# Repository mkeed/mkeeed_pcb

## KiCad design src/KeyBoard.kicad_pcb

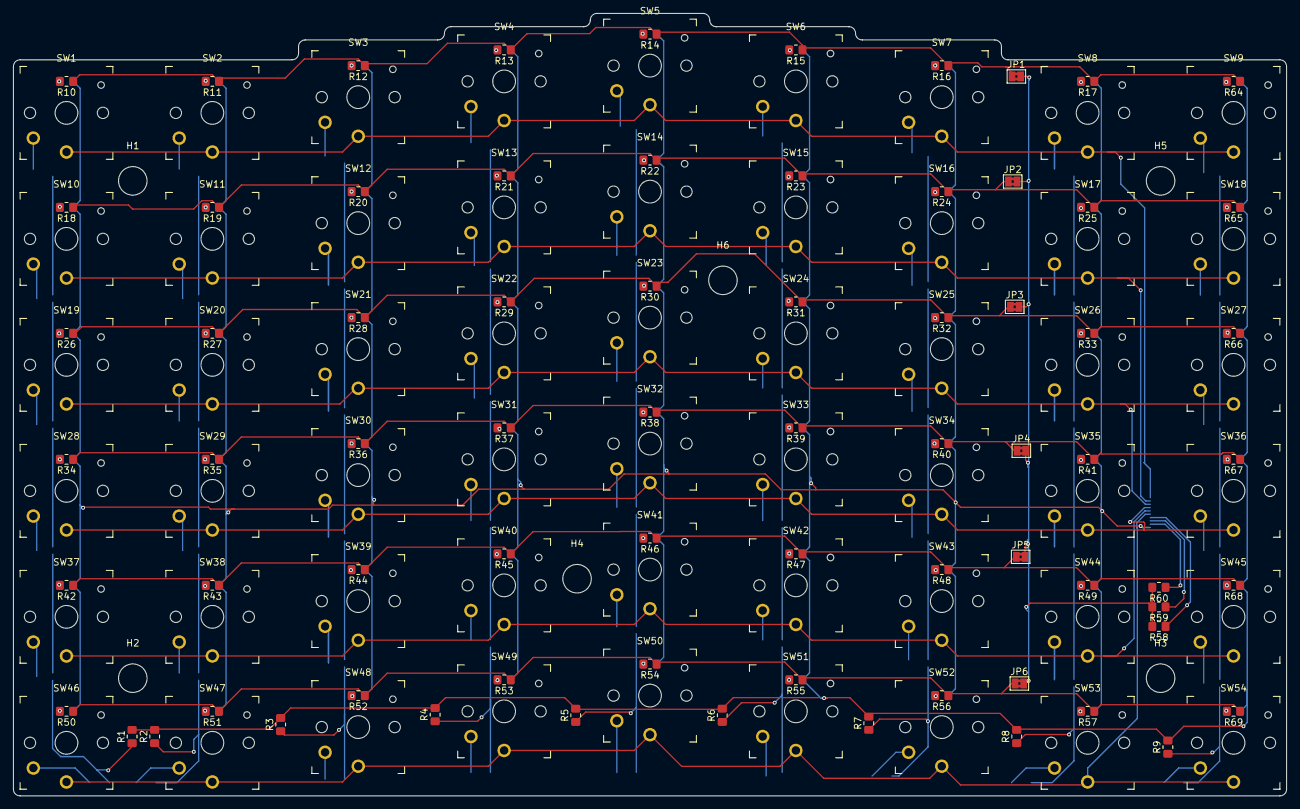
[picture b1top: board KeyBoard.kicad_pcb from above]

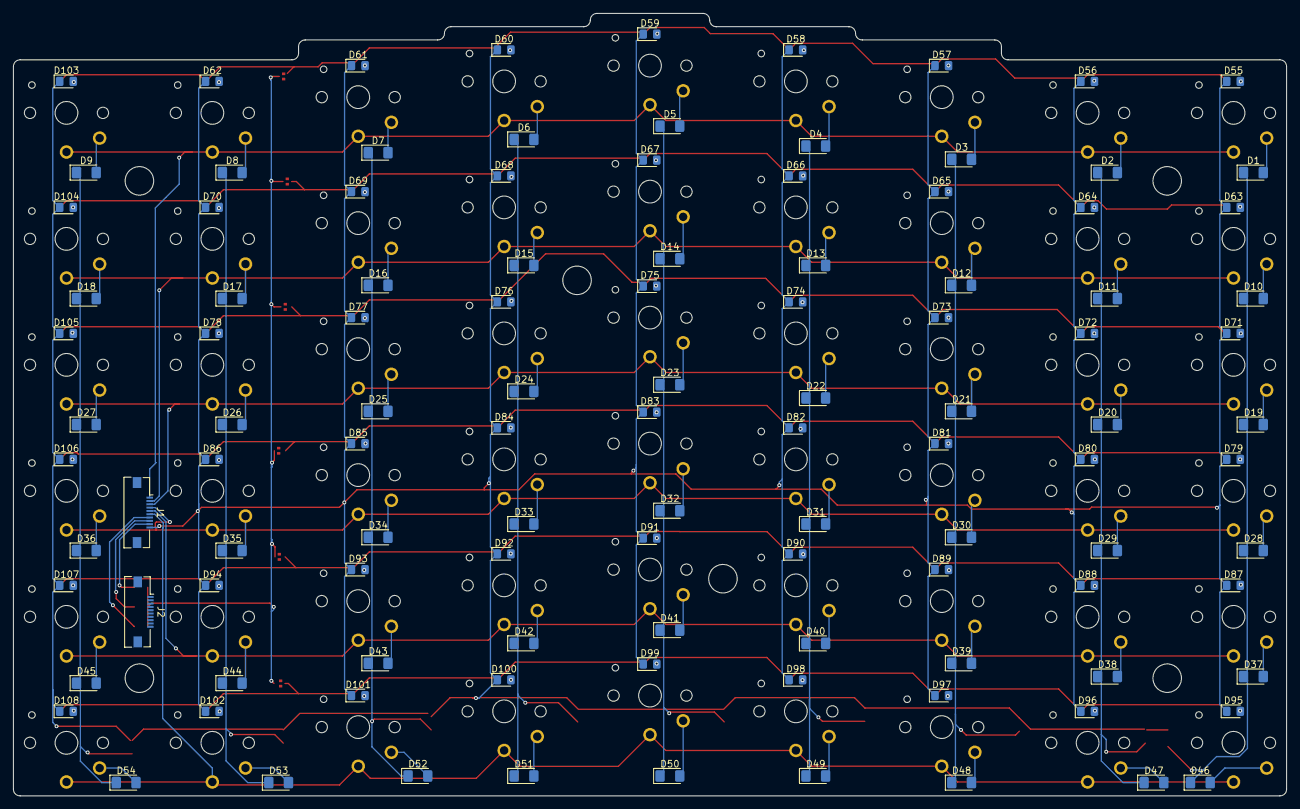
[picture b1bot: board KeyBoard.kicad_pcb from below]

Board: 2 copper layers, 192.0 x 118.0 mm, 242 parts (110 on the bottom side), 134 nets.

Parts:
D1, D2, D3, D4, D5, D6, D7, D8, D9, D10, D11, D12, D13, D14, D15, D16, D17, D18, D19, D20, D21, D22, D23, D24, D25, D26, D27, D28, D29, D30, D31, D32, D33, D34, D35, D36, D37, D38, D39, D40, D41, D42, D43, D44, D45, D46, D47, D48, D49, D50, D51, D52, D53, D54: D; D_1206_3216Metric_Pad1.42x1.75mm_HandSolder
D55, D56, D57, D58, D59, D60, D61, D62, D63, D64, D65, D66, D67, D68, D69, D70, D71, D72, D73, D74, D75, D76, D77, D78, D79, D80, D81, D82, D83, D84, D85, D86, D87, D88, D89, D90, D91, D92, D93, D94, D95, D96, D97, D98, D99, D100, D101, D102, D103, D104, D105, D106, D107, D108: LED; LED_0805_2012Metric_Pad1.15x1.40mm_HandSolder
H1, H2, H3, H4, H5, H6: MountingHole; MountingHole_4.3mm_M4
J1, J2: Conn_01x10_Shielded; Molex_54548-1071_1x10-1MP_P0.5mm_Horizontal
JP1, JP2, JP3, JP4, JP5, JP6: jump; SolderJumper-2_P1.3mm_Bridged2Bar_Pad1.0x1.5mm
R1, R2, R3, R4, R5, R6, R7, R8, R9, R10, R11, R12, R13, R14, R15, R16, R17, R18, R19, R20, R21, R22, R23, R24, R25, R26, R27, R28, R29, R30, R31, R32, R33, R34, R35, R36, R37, R38, R39, R40, R41, R42, R43, R44, R45, R46, R47, R48, R49, R50, R51, R52, R53, R54, R55, R56, R57, R58, R59, R60, R64, R65, R66, R67, R68, R69: R; R_0805_2012Metric_Pad1.20x1.40mm_HandSolder
SW1, SW2, SW3, SW4, SW5, SW6, SW7, SW8, SW9, SW10, SW11, SW12, SW13, SW14, SW15, SW16, SW17, SW18, SW19, SW20, SW21, SW22, SW23, SW24, SW25, SW26, SW27, SW28, SW29, SW30, SW31, SW32, SW33, SW34, SW35, SW36, SW37, SW38, SW39, SW40, SW41, SW42, SW43, SW44, SW45, SW46, SW47, SW48, SW49, SW50, SW51, SW52, SW53, SW54: SW_Push; SW_PG1350

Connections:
/D1: D1.1 (K), D10.1 (K), D19.1 (K), D28.1 (K), D37.1 (K), D46.1 (K), J2.1, R1.1
/D2: D2.1 (K), D11.1 (K), D20.1 (K), D29.1 (K), D38.1 (K), D47.1 (K), J2.2, R2.1
/D3: D3.1 (K), D12.1 (K), D21.1 (K), D30.1 (K), D39.1 (K), D48.1 (K), J2.3, R3.1
/D4: D4.1 (K), D13.1 (K), D22.1 (K), D31.1 (K), D40.1 (K), D49.1 (K), J2.4, R4.1
/D5: D5.1 (K), D14.1 (K), D23.1 (K), D32.1 (K), D41.1 (K), D50.1 (K), J2.5, R5.1
/D6: D6.1 (K), D15.1 (K), D24.1 (K), D33.1 (K), D42.1 (K), D51.1 (K), J2.6, R6.1
/D7: D7.1 (K), D16.1 (K), D25.1 (K), D34.1 (K), D43.1 (K), D52.1 (K), J2.7, R7.1
/D8: D8.1 (K), D17.1 (K), D26.1 (K), D35.1 (K), D44.1 (K), D53.1 (K), J2.8, R8.1
/D9: D9.1 (K), D18.1 (K), D27.1 (K), D36.1 (K), D45.1 (K), D54.1 (K), J2.9, R9.1
/R1: J1.1, SW1.1, SW2.1, SW3.1, SW4.1, SW5.1, SW6.1, SW7.1, SW8.1, SW9.1
/R2: J1.2, SW10.1, SW11.1, SW12.1, SW13.1, SW14.1, SW15.1, SW16.1, SW17.1, SW18.1
/R3: J1.3, SW19.1, SW20.1, SW21.1, SW22.1, SW23.1, SW24.1, SW25.1, SW26.1, SW27.1
/R4: J1.4, SW28.1, SW29.1, SW30.1, SW31.1, SW32.1, SW33.1, SW34.1, SW35.1, SW36.1
/R5: J1.5, SW37.1, SW38.1, SW39.1, SW40.1, SW41.1, SW42.1, SW43.1, SW44.1, SW45.1
/R6: J1.6, SW46.1, SW47.1, SW48.1, SW49.1, SW50.1, SW51.1, SW52.1, SW53.1, SW54.1
GND: D55.1 (K), D56.1 (K), D57.1 (K), D58.1 (K), D59.1 (K), D60.1 (K), D61.1 (K), D62.1 (K), D63.1 (K), D64.1 (K), D65.1 (K), D66.1 (K), D67.1 (K), D68.1 (K), D69.1 (K), D70.1 (K), D71.1 (K), D72.1 (K), D73.1 (K), D74.1 (K), D75.1 (K), D76.1 (K), D77.1 (K), D78.1 (K), D79.1 (K), D80.1 (K), D81.1 (K), D82.1 (K), D83.1 (K), D84.1 (K), D85.1 (K), D86.1 (K), D87.1 (K), D88.1 (K), D89.1 (K), D90.1 (K), D91.1 (K), D92.1 (K), D93.1 (K), D94.1 (K), D95.1 (K), D96.1 (K), D97.1 (K), D98.1 (K), D99.1 (K), D100.1 (K), D101.1 (K), D102.1 (K), D103.1 (K), D104.1 (K), D105.1 (K), D106.1 (K), D107.1 (K), D108.1 (K), J1.10, R1.2, R2.2, R3.2, R4.2, R5.2, R6.2, R7.2, R8.2, R9.2
unnamed: D1.2 (A), SW1.2
unnamed: D2.2 (A), SW2.2
unnamed: D3.2 (A), SW3.2
unnamed: D4.2 (A), SW4.2
unnamed: D5.2 (A), SW5.2
unnamed: D6.2 (A), SW6.2
unnamed: D7.2 (A), SW7.2
unnamed: D8.2 (A), SW8.2
unnamed: D9.2 (A), SW9.2
unnamed: D10.2 (A), SW10.2
unnamed: D11.2 (A), SW11.2
unnamed: D12.2 (A), SW12.2
unnamed: D13.2 (A), SW13.2
unnamed: D14.2 (A), SW14.2
unnamed: D15.2 (A), SW15.2
unnamed: D16.2 (A), SW16.2
unnamed: D17.2 (A), SW17.2
unnamed: D18.2 (A), SW18.2
unnamed: D19.2 (A), SW19.2
unnamed: D20.2 (A), SW20.2
unnamed: D21.2 (A), SW21.2
unnamed: D22.2 (A), SW22.2
unnamed: D23.2 (A), SW23.2
unnamed: D24.2 (A), SW24.2
unnamed: D25.2 (A), SW25.2
unnamed: D26.2 (A), SW26.2
unnamed: D27.2 (A), SW27.2
unnamed: D28.2 (A), SW28.2
unnamed: D29.2 (A), SW29.2
unnamed: D30.2 (A), SW30.2
unnamed: D31.2 (A), SW31.2
unnamed: D32.2 (A), SW32.2
unnamed: D33.2 (A), SW33.2
unnamed: D34.2 (A), SW34.2
unnamed: D35.2 (A), SW35.2
unnamed: D36.2 (A), SW36.2
unnamed: D37.2 (A), SW37.2
unnamed: D38.2 (A), SW38.2
unnamed: D39.2 (A), SW39.2
unnamed: D40.2 (A), SW40.2
unnamed: D41.2 (A), SW41.2
unnamed: D42.2 (A), SW42.2
unnamed: D43.2 (A), SW43.2
unnamed: D44.2 (A), SW44.2
unnamed: D45.2 (A), SW45.2
unnamed: D46.2 (A), SW46.2
unnamed: D47.2 (A), SW47.2
unnamed: D48.2 (A), SW48.2
unnamed: D49.2 (A), SW49.2
unnamed: D50.2 (A), SW50.2
unnamed: D51.2 (A), SW51.2
unnamed: D52.2 (A), SW52.2
unnamed: D53.2 (A), SW53.2
unnamed: D54.2 (A), SW54.2
unnamed: D55.2 (A), R10.2
unnamed: D56.2 (A), R11.2
unnamed: D57.2 (A), R12.2
unnamed: D58.2 (A), R13.2
unnamed: D59.2 (A), R14.2
unnamed: D60.2 (A), R15.2
unnamed: D61.2 (A), R16.2
unnamed: D62.2 (A), R17.2
unnamed: D63.2 (A), R18.2
unnamed: D64.2 (A), R19.2
unnamed: D65.2 (A), R20.2
unnamed: D66.2 (A), R21.2
unnamed: D67.2 (A), R22.2
unnamed: D68.2 (A), R23.2
unnamed: D69.2 (A), R24.2
unnamed: D70.2 (A), R25.2
unnamed: D71.2 (A), R26.2
unnamed: D72.2 (A), R27.2
unnamed: D73.2 (A), R28.2
unnamed: D74.2 (A), R29.2
unnamed: D75.2 (A), R30.2
unnamed: D76.2 (A), R31.2
unnamed: D77.2 (A), R32.2
unnamed: D78.2 (A), R33.2
unnamed: D79.2 (A), R34.2
unnamed: D80.2 (A), R35.2
unnamed: D81.2 (A), R36.2
unnamed: D82.2 (A), R37.2
unnamed: D83.2 (A), R38.2
unnamed: D84.2 (A), R39.2
unnamed: D85.2 (A), R40.2
unnamed: D86.2 (A), R41.2
unnamed: D87.2 (A), R42.2
unnamed: D88.2 (A), R43.2
unnamed: D89.2 (A), R44.2
unnamed: D90.2 (A), R45.2
unnamed: D91.2 (A), R46.2
unnamed: D92.2 (A), R47.2
unnamed: D93.2 (A), R48.2
unnamed: D94.2 (A), R49.2
unnamed: D95.2 (A), R50.2
unnamed: D96.2 (A), R51.2
unnamed: D97.2 (A), R52.2
unnamed: D98.2 (A), R53.2
unnamed: D99.2 (A), R54.2
unnamed: D100.2 (A), R55.2
unnamed: D101.2 (A), R56.2
unnamed: D102.2 (A), R57.2
unnamed: D103.2 (A), R64.2
unnamed: D104.2 (A), R65.2
unnamed: D105.2 (A), R66.2
unnamed: D106.2 (A), R67.2
unnamed: D107.2 (A), R68.2
unnamed: D108.2 (A), R69.2
unnamed: J1.7, R58.1
unnamed: J1.8, R59.1
unnamed: J1.9, R60.1
unnamed: JP1.1 (A), R10.1, R11.1, R12.1, R13.1, R14.1, R15.1, R16.1, R17.1, R64.1
unnamed: JP1.2 (B), JP2.2 (B), JP3.2 (B), JP4.2 (B), JP5.2 (B), JP6.2 (B), R58.2, R59.2, R60.2
unnamed: JP2.1 (A), R18.1, R19.1, R20.1, R21.1, R22.1, R23.1, R24.1, R25.1, R65.1
unnamed: JP3.1 (A), R26.1, R27.1, R28.1, R29.1, R30.1, R31.1, R32.1, R33.1, R66.1
unnamed: JP4.1 (A), R34.1, R35.1, R36.1, R37.1, R38.1, R39.1, R40.1, R41.1, R67.1
unnamed: JP5.1 (A), R42.1, R43.1, R44.1, R45.1, R46.1, R47.1, R48.1, R49.1, R68.1
unnamed: JP6.1 (A), R50.1, R51.1, R52.1, R53.1, R54.1, R55.1, R56.1, R57.1, R69.1

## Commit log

2025-05-04 initial code
2025-05-05 work
2025-05-10 updated crosshair to be offset correctly
2025-05-10 crosshair more fix
